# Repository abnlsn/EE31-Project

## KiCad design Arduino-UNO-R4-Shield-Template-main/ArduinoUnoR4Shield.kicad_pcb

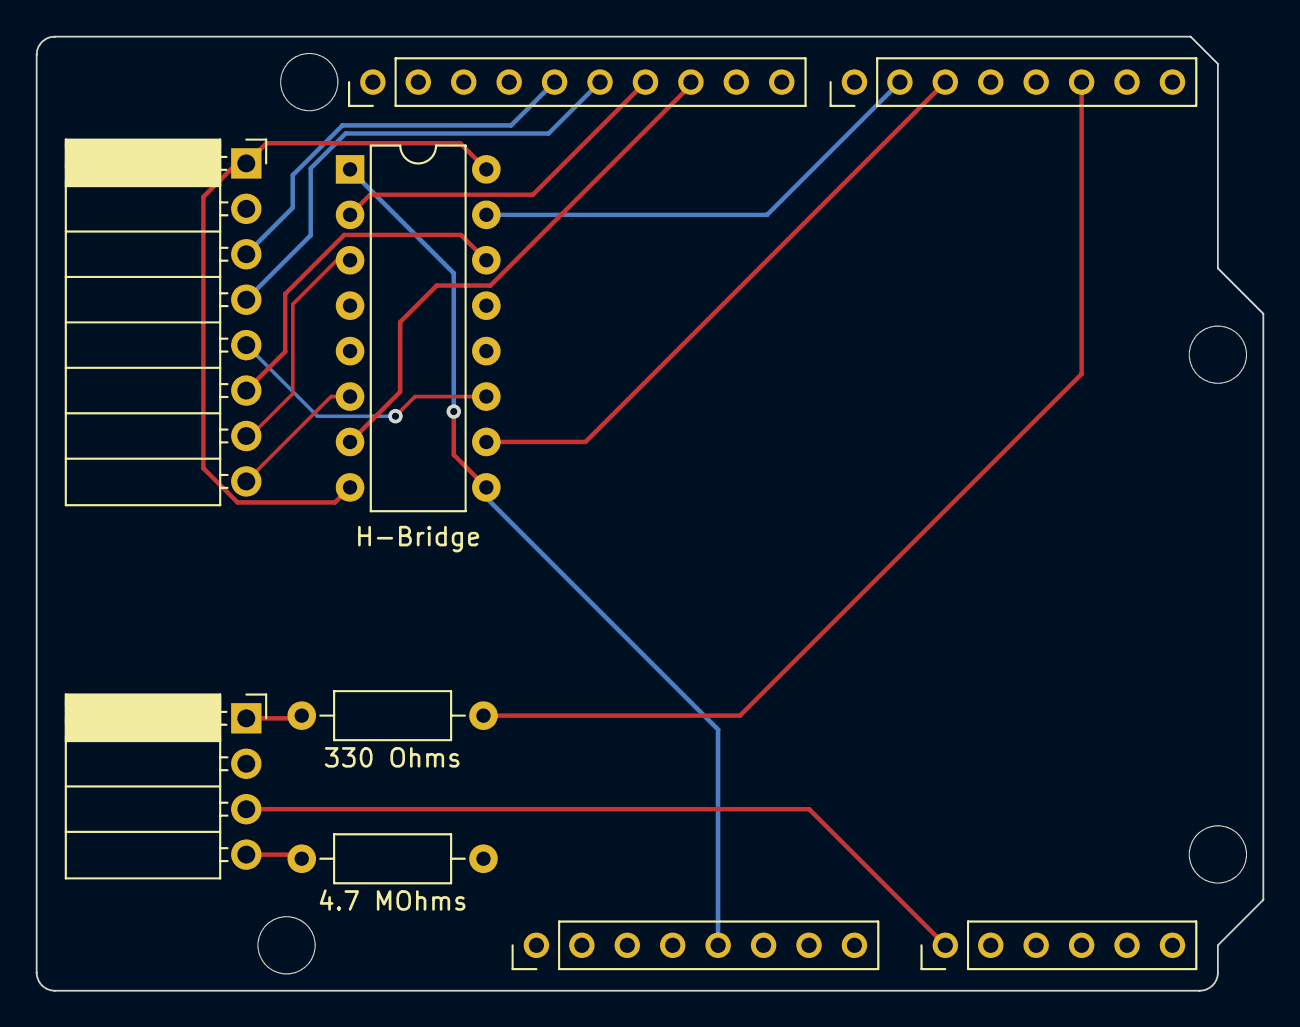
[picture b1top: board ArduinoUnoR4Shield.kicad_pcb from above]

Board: 2 copper layers, 68.6 x 53.3 mm, 13 parts (0 on the bottom side), 17 nets.

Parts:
4.7 MOhms: 4.7 MOhms; R_Axial_DIN0207_L6.3mm_D2.5mm_P10.16mm_Horizontal
330 Ohms: 330 Ohms; R_Axial_DIN0207_L6.3mm_D2.5mm_P10.16mm_Horizontal
H1: MountingHole1; Arduino_MountingHole
H2: MountingHole2; Arduino_MountingHole
H3: MountingHole3; Arduino_MountingHole
H4: MountingHole4; Arduino_MountingHole
H-Bridge: L293; DIP-16_W7.62mm
J1: Conn_01x08_Socket; PinSocket_1x08_P2.54mm_Horizontal
J2: Conn_01x04_Socket; PinSocket_1x04_P2.54mm_Horizontal
U2: Analog_1; Arduino_PinSocket_1x08_P2.54mm_Vertical
U3: Analog_2; Arduino_PinSocket_1x06_P2.54mm_Vertical
U6: Digital_1; Arduino_PinSocket_1x10_P2.54mm_Vertical
U7: Digital_2; Arduino_PinSocket_1x08_P2.54mm_Vertical

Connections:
5V: H-Bridge.1 (EN1,2), H-Bridge.9 (EN3,4), U2.5 (+5V)
6V: H-Bridge.8 (VCC2), H-Bridge.16 (VCC1), J1.1
GND: 4.7 MOhms.1, H-Bridge.4 (GND), H-Bridge.5 (GND), H-Bridge.12 (GND), H-Bridge.13 (GND), J1.2, J2.2, U2.7 (GND)
L encoder: J1.4, U6.6 (D12/CIPO)
L motor 1: H-Bridge.2 (1A), U6.7 (~D11/COPI)
L motor 2: H-Bridge.7 (2A), U6.8 (~D10/CS/CANTX0)
unnamed: 330 Ohms.2, J2.1
unnamed: J2.3, U3.9 (A0)
unnamed: 4.7 MOhms.2, J2.4
unnamed: 330 Ohms.1, U7.16 (D2)
R encoder: J1.3, U6.5 (D13/SCK/CANRX0)
R motor 1: H-Bridge.10 (3A), U7.13 (~D5)
R motor 2: H-Bridge.15 (4A), U7.12 (~D6)
left motor +: H-Bridge.3 (1Y), J1.7
left motor -: H-Bridge.6 (2Y), J1.8
right motor +: H-Bridge.11 (3Y), J1.5
right motor -: H-Bridge.14 (4Y), J1.6

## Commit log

2024-09-12 test commit
2024-09-12 Basic H_bridge PWM code
2024-09-17 state machine
2024-09-19 initial GET requests working using WiFiNINA
2024-09-26 HTTP requests momentarily not working, will fix
2024-09-26 Got GET / variable name parsing working
2024-09-26 Combined state machine and wifi code
2024-10-01 Added dynamic url based on UUIDs in arduino_secrets.h
2024-10-01 Finished integration with state machine, it is working on physical bot!
2024-10-03 Added simple Web remote for robot
2024-10-15 Got speed calculations working!
2024-10-15 Copied motor drive code into sketch
2024-10-15 Debug script for graphing speed vs duty cycle
2024-10-17 Rudimentary motor straightening working
2024-10-22 Added motor dependent calibration values
2024-10-24 Refactoring
2024-10-24 Added direction + offset control
2024-10-29 Integrating into state machine
2024-10-29 Fixed duty cycle problems with right motor
2024-10-31 Updated pins to use PWM
2024-11-14 Working on motor safety
2024-11-14 Got working with websockets
2024-11-19 Refactoring files
2024-11-19 Added state machine structure
2024-11-21 Changed filenames
2024-11-21 Got rotation working in the motorspeed state machine
2024-11-26 Added color sensing/line following functionality
2024-11-26 Added rotation constants, still need to calibrate
2024-12-03 Added loop for reading color values, integrated with line following
2024-12-03 Added ambient light adjustment to color sensing
2024-12-06 Added comments
2024-12-06 First attempt at color sensing
2024-12-08 Updated line following
2024-12-08 Changed pins
2024-12-09 Updated pins, improved state machine
2024-12-09 Integrated websocket code into state machine
2024-12-09 Added debug over wifi
2024-12-10 Got color sensing working
2024-12-11 Initial linefollowing is working
2024-12-13 Tweaking config values
2024-12-14 Switched motors for left turns
2024-12-16 Updating calibration values from remote_control branch
2024-12-18 Group demo attempt
2024-12-18 Updated for Bot 2 solo demo
2024-12-18 Cleaning up repo
2024-12-18 CAD Files
    Added CAD files
2024-12-18 Updated Comments
